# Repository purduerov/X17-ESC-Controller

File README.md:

# X17-ESC-Controller
This board turns signals from the Pi into PWM signals that go to the ESC Adapter

Whenever you make a new part, download the datasheet and save it here _**and**_ with the part in the parts library

Always pull other people's changes before beginning to work
`git pull`

Be sure to push your changes after  working on them. Run:
1. `git add .` to add any files in this directory or a subdirectory
or `git add -u` to add any modified files
2. (Optional) `git clean -nX` to see what ignored files can be removed
	`git clean -fX` removes ignored files (Eagle backups)
3. `git commit -m "helpful commit message"` with a description of the work that you did
4. `git push` to push your work to github

Other helpful commands
* `git status` says information about modified and staged files
* `git log` shows the recent commits of the repository
* `git log filename.extension` show the recent commits for just that file
* `git checkout first-couple-letter-of-commit-id` lets you go back to a previous version
* `git checkout master` brings you back to the latest commit
* `git tag` lists the tags
* `git tag -a orderX -m "the version of the board placed for the X'th order"` tag a specific commit
* `git push --tags` needed to push tags to remote
* `git show orderX` show the commit log for the given tag
* `git checkout orderX` go back and interact with the files at the tagged commit

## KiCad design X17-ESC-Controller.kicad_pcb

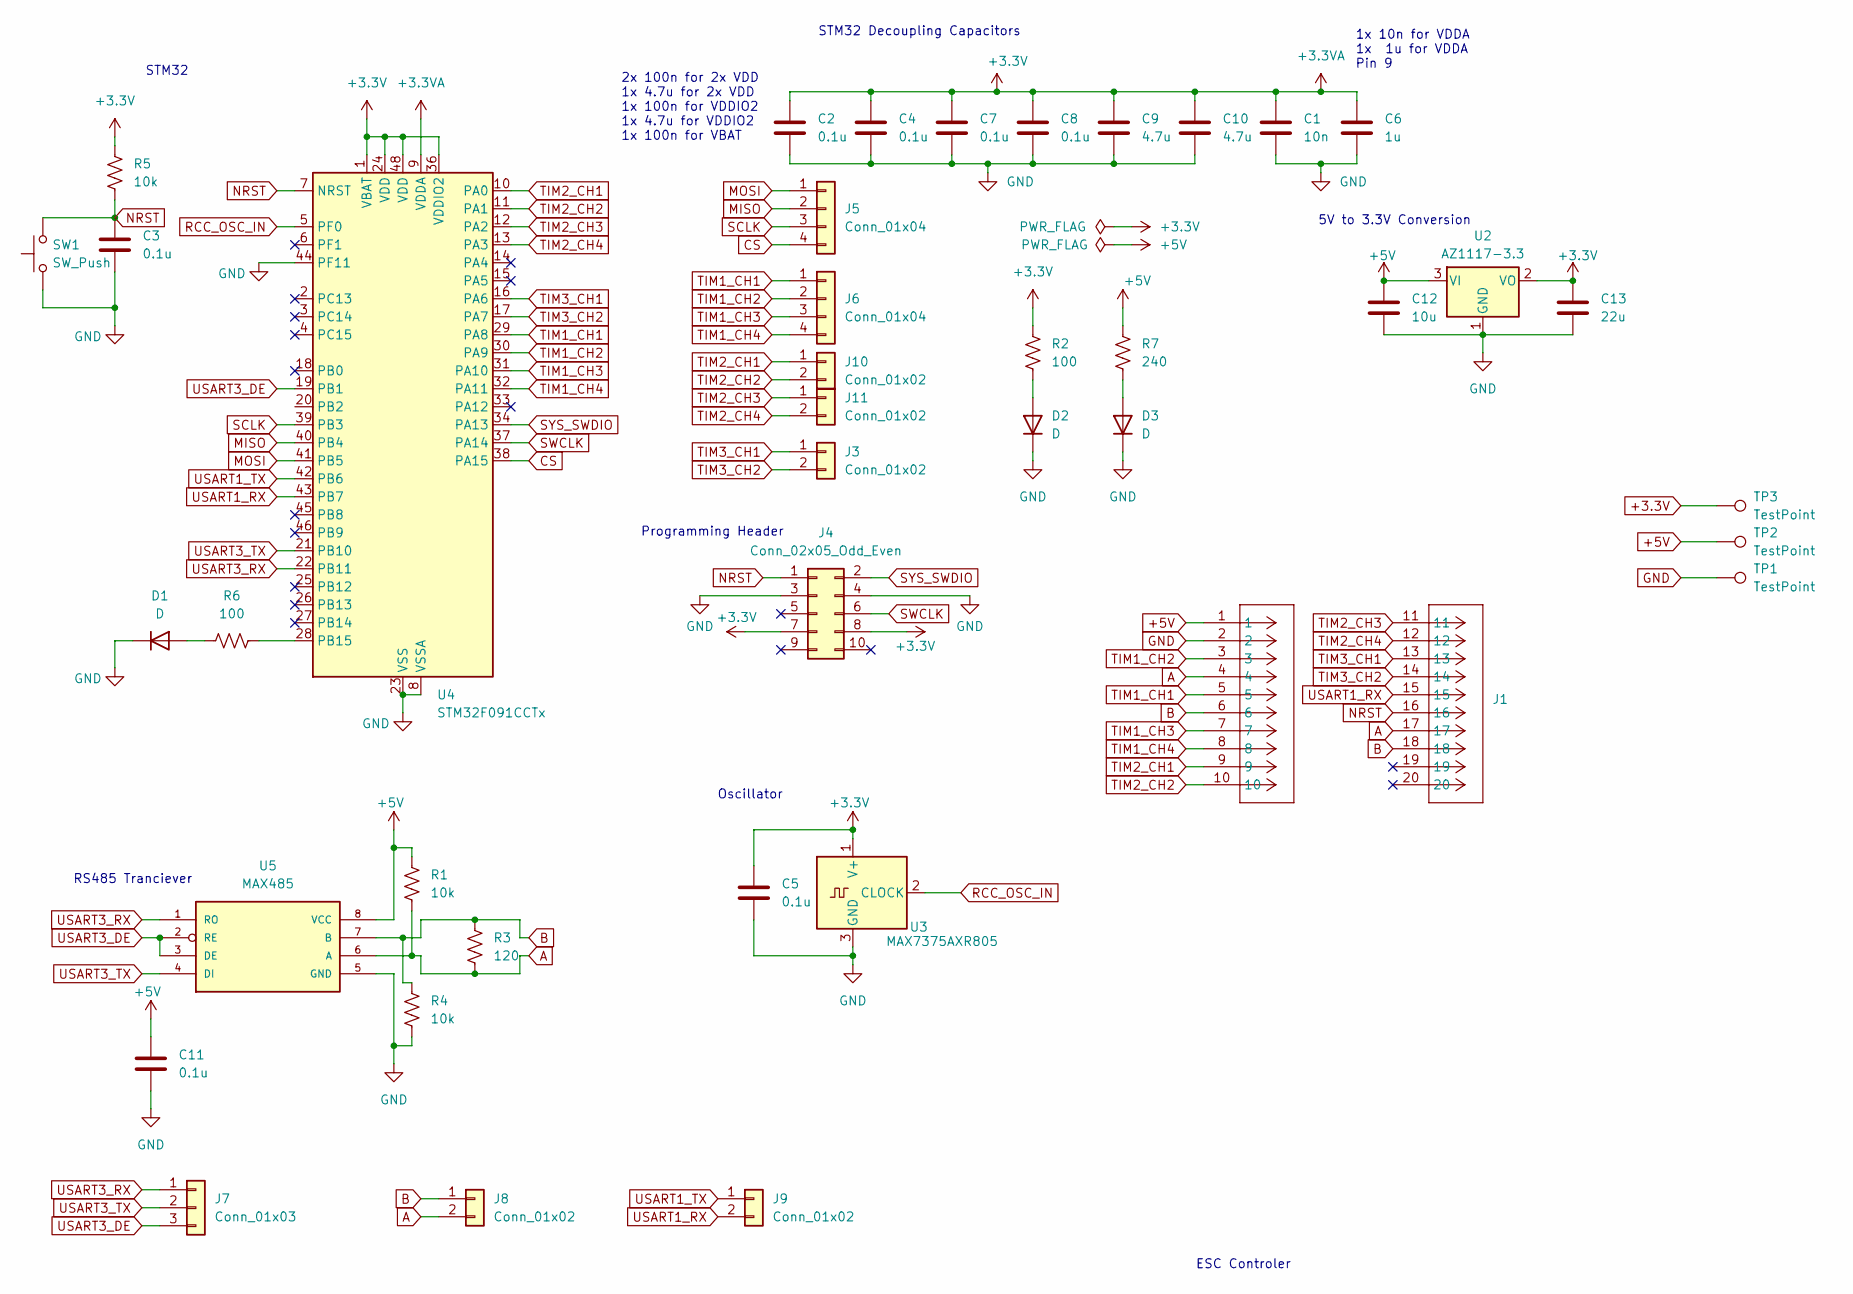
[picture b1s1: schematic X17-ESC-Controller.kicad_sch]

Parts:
C1: 10n; C_0603_1608Metric_Pad1.08x0.95mm_HandSolder
C2, C3, C4, C5, C7, C8, C11: 0.1u; C_0603_1608Metric_Pad1.08x0.95mm_HandSolder
C6: 1u; C_0603_1608Metric_Pad1.08x0.95mm_HandSolder
C9, C10: 4.7u; C_0603_1608Metric_Pad1.08x0.95mm_HandSolder
C12: 10u; C_0603_1608Metric_Pad1.08x0.95mm_HandSolder
C13: 22u; C_0603_1608Metric_Pad1.08x0.95mm_HandSolder
D1, D2, D3: D; LED_0805_2012Metric_Pad1.15x1.40mm_HandSolder
J1: CON10_2X5_UF_DF11_HIR
J3, J8, J9, J10, J11: Conn_01x02; PinHeader_1x02_P2.54mm_Vertical
J4: Conn_02x05_Odd_Even; IDC-Header_2x05_P2.54mm_Vertical
J5, J6: Conn_01x04; PinHeader_1x04_P2.54mm_Vertical
J7: Conn_01x03; PinHeader_1x03_P2.54mm_Vertical
R1, R4, R5: 10k; R_0603_1608Metric_Pad0.98x0.95mm_HandSolder
R2, R6: 100; R_0603_1608Metric_Pad0.98x0.95mm_HandSolder
R3: 120; R_0603_1608Metric_Pad0.98x0.95mm_HandSolder
R7: 240; R_0603_1608Metric_Pad0.98x0.95mm_HandSolder
SW1: SW_Push; SW_FSM2JMTR_TEC
TP1, TP2, TP3: TestPoint; TestPoint_Pad_D4.0mm
U2: AZ1117-3.3; SOT-223-3_TabPin2
U3: MAX7375AXR805; SOT-323_SC-70_Handsoldering
U4: STM32F091CCTx; LQFP-48_7x7mm_P0.5mm
U5: MAX485; SO08

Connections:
+3.3V: C1.1, C2.1, C4.1, C5.1, C6.1, C7.1, C8.1, C9.1, C10.1, C13.1, J4.7, J4.8, R2.2, R5.2, TP3.1, U2.2 (VO), U3.1 (V+), U4.1 (VBAT), U4.9 (VDDA), U4.24 (VDD), U4.36 (VDDIO2), U4.48 (VDD)
+5V: C11.1, C12.1, J1.1, R1.2, R7.2, TP2.1, U2.3 (VI), U5.8 (VCC)
A: J1.4, J1.17, J8.2, R1.1, R3.2, U5.6 (A)
B: J1.6, J1.18, J8.1, R3.1, R4.2, U5.7 (B)
CS: J5.4, U4.38 (PA15)
GND: C1.2, C2.2, C3.2, C4.2, C5.2, C6.2, C7.2, C8.2, C9.2, C10.2, C11.2, C12.2, C13.2, D1.1 (K), D2.1 (K), D3.1 (K), J1.2, J4.3, J4.4, R4.1, SW1.1, TP1.1, U2.1 (GND), U3.3 (GND), U4.8 (VSSA), U4.23 (VSS), U4.35 (VSS), U4.44 (PF11), U4.47 (VSS), U5.5 (GND)
MISO: J5.2, U4.40 (PB4)
MOSI: J5.1, U4.41 (PB5)
NRST: C3.1, J1.16, J4.1, R5.1, SW1.2, U4.7 (NRST)
unnamed: D1.2 (A), R6.1
unnamed: D2.2 (A), R2.1
unnamed: D3.2 (A), R7.1
unnamed: R6.2, U4.28 (PB15)
RCC_OSC_IN: U3.2 (CLOCK), U4.5 (PF0)
SCLK: J5.3, U4.39 (PB3)
SWCLK: J4.6, U4.37 (PA14)
SYS_SWDIO: J4.2, U4.34 (PA13)
TIM1_CH1: J1.5, J6.1, U4.29 (PA8)
TIM1_CH2: J1.3, J6.2, U4.30 (PA9)
TIM1_CH3: J1.7, J6.3, U4.31 (PA10)
TIM1_CH4: J1.8, J6.4, U4.32 (PA11)
TIM2_CH1: J1.9, J10.1, U4.10 (PA0)
TIM2_CH2: J1.10, J10.2, U4.11 (PA1)
TIM2_CH3: J1.11, J11.1, U4.12 (PA2)
TIM2_CH4: J1.12, J11.2, U4.13 (PA3)
TIM3_CH1: J1.13, J3.1, U4.16 (PA6)
TIM3_CH2: J1.14, J3.2, U4.17 (PA7)
USART1_RX: J1.15, J9.2, U4.43 (PB7)
USART1_TX: J9.1, U4.42 (PB6)
USART3_DE: J7.3, U4.19 (PB1), U5.2 (RE), U5.3 (DE)
USART3_RX: J7.1, U4.22 (PB11), U5.1 (RO)
USART3_TX: J7.2, U4.21 (PB10), U5.4 (DI)

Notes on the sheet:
STM32
Programming Header
2x 100n for 2x VDD 1x 4.7u for 2x VDD 1x 100n for VDDIO2 1x 4.7u for VDDIO2 1x 100n for VBAT
1x 10n for VDDA 1x 1u for VDDA Pin 9
5V to 3.3V Conversion
Oscillator
ESC Controler
STM32 Decoupling Capacitors
RS485 Tranciever

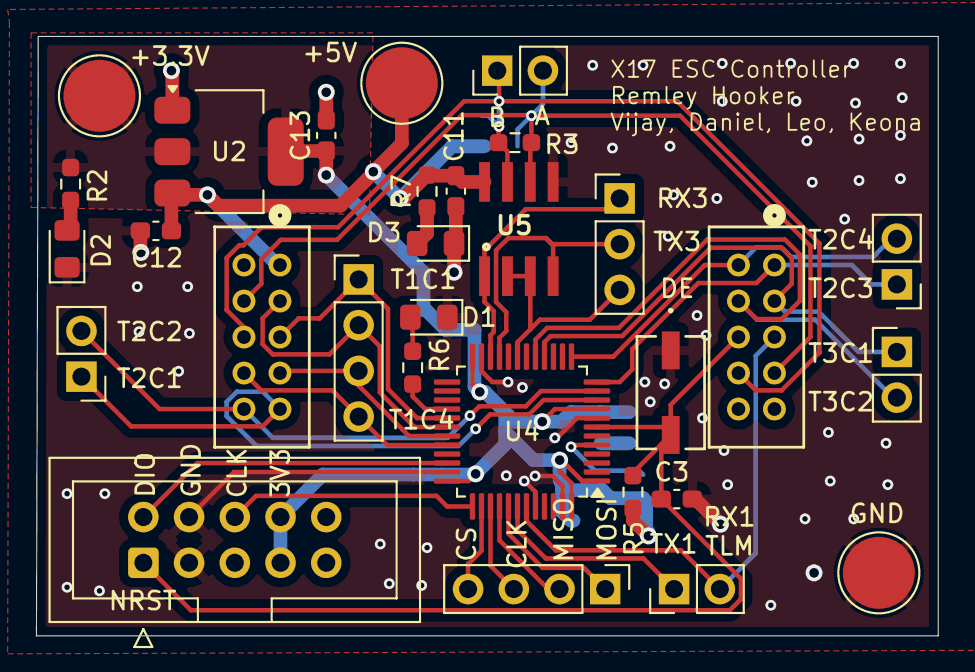
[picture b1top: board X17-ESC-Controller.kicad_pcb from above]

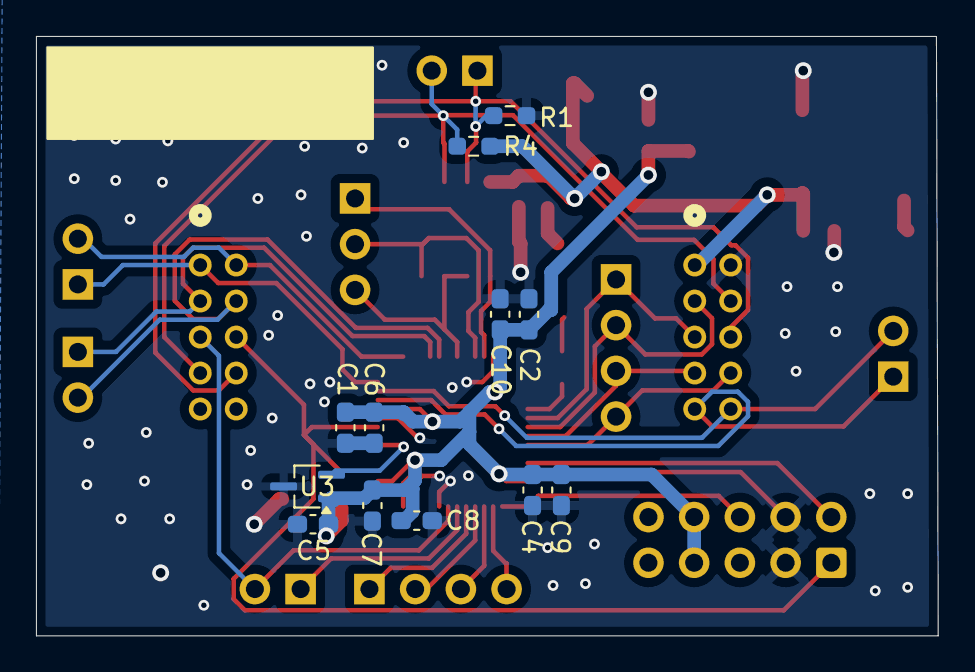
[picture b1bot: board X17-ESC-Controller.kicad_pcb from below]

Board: 2 copper layers, 50.1 x 33.3 mm, 41 parts (12 on the bottom side), 32 nets.

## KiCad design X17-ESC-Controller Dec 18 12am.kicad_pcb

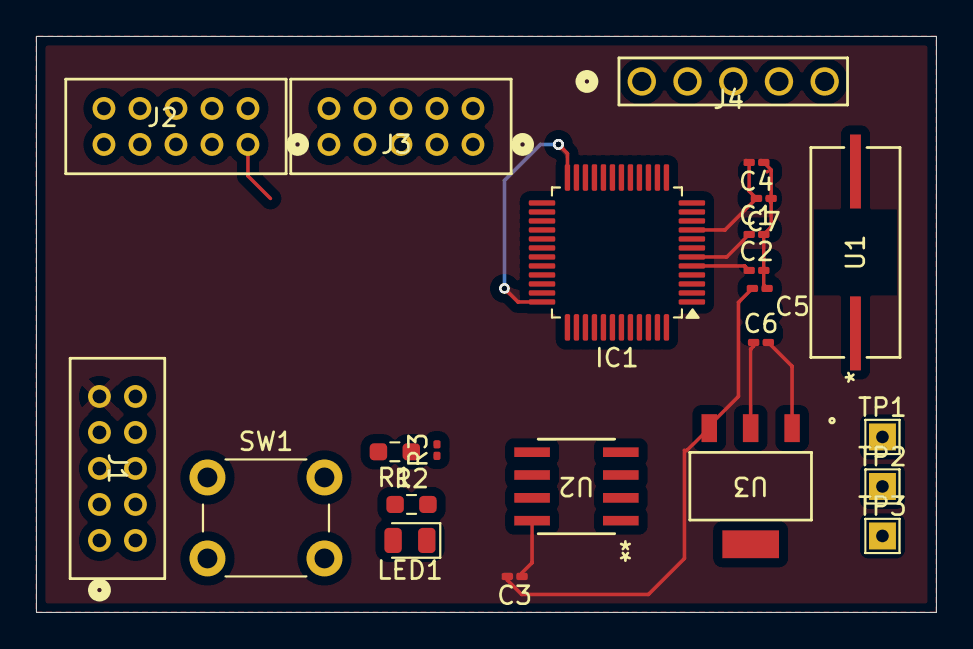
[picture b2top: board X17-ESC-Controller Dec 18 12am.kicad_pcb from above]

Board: 2 copper layers, 50.0 x 32.0 mm, 23 parts (0 on the bottom side), 33 nets.

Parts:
C1, C2: 18pF; C_0201_0603Metric_Pad0.64x0.40mm_HandSolder
C3: CL10B104KB8NNWC; C_0201_0603Metric_Pad0.64x0.40mm_HandSolder
C4, C7: C; C_0201_0603Metric_Pad0.64x0.40mm_HandSolder
C5, C6: GRM188R60G226MEA0D; C_0201_0603Metric_Pad0.64x0.40mm_HandSolder
IC1: STM32F091CCT7; LQFP-48_7x7mm_P0.5mm
J1: CON10_2X5_UF_DF11_HIR
J2, J3: DF11-10DP-2DSA24; CON10_2X5_UF_DF11_HIR
J4: Conn_2Rows-05Pins; CONN_A-4030-05A_MOL
LED1: APT2012SGC; LED_0805_2012Metric
R1: 20k; R_0603_1608Metric_Pad0.98x0.95mm_HandSolder
R2: 4.2k; R_0603_1608Metric_Pad0.98x0.95mm_HandSolder
R3: 10k; R_0201_0603Metric
SW1: SW_Push; SW_PUSH_6mm
TP1, TP2, TP3: TestPoint; TestPoint_THTPad_1.5x1.5mm_Drill0.7mm
U1: 8mHz; ABLS-8.000MHZ-B2-T_ABR
U2: MAX485CSA+T; 21-0041-3-M_90-0096-8L_MXM
U3: SOT223_AZ1117I_6P5X3P5_DIO

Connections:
+5V: C3.2, C5.2, U3.3 (INPUT)
/-3.3V: C6.1, U3.2 (OUTPUT)
/NC: IC1.1 (VBAT), IC1.2 (PC13), IC1.3 (PC14-OSC32_IN), IC1.4 (PC15-OSC32_OUT), IC1.8 (VSSA), IC1.20 (PB2), IC1.25 (PB12), IC1.26 (PB13), IC1.27 (PB14), IC1.35 (VSS_2), IC1.38 (PA15), IC1.39 (PB3), IC1.46 (PB9), IC1.47 (VSS_3), J1.1, J1.5, J1.8, J1.10
A: J2.3, U2.6 (A)
B: J2.4, R1.1, U2.7 (B)
CS: IC1.14 (PA4), J3.10, J4.4
GND: C1.2, C2.2, C4.1, C5.1, C6.2, C7.1, IC1.23 (VSS_1), IC1.44 (PF11-BOOT0), IC1.45 (PB8), IC1.48 (VDD_2), J1.3, J1.4, J4.5, LED1.1, R1.2, SW1.2, TP1.1, U2.5 (GND), U3.1 (ADJ/GND)
LED: IC1.28 (PB15), R2.1
MISO: IC1.16 (PA6), J3.7, J4.2
MOSI: IC1.17 (PA7), J3.8, J4.1
NRST: IC1.7 (NRST), J3.6, R3.2, SW1.1
unnamed: LED1.2, R2.2
unnamed: C3.1, U2.8 (VCC)
RCC_OSC_IN: C2.1, IC1.5 (PF0-OSC_IN), U1.2
RCC_OSC_OUT: C1.1, IC1.6 (PF1-OSC_OUT), U1.1
SCLK: IC1.15 (PA5), J3.9
SWCLK: IC1.37 (PA14), J1.6
SYS_SWDIO: IC1.34 (PA13), J1.2
TIM1_CH1: IC1.29 (PA8), J2.5
TIM1_CH2: IC1.30 (PA9), J2.6
TIM1_CH3: IC1.31 (PA10), J2.7
TIM1_CH4: IC1.32 (PA11), J2.8
TIM2_CH1: IC1.10 (PA0), J2.9
TIM2_CH2: IC1.11 (PA1), J2.10
TIM2_CH3: IC1.12 (PA2), J3.1
TIM2_CH4: IC1.13 (PA3), J3.2
TIM3_CH1: IC1.40 (PB4), J3.3
TIM3_CH2: IC1.41 (PB5), J3.4
USART1_DE: IC1.33 (PA12), U2.2 (*RE), U2.3 (DE)
USART1_RX: IC1.43 (PB7), U2.1 (RO)
USART1_TX: IC1.42 (PB6), U2.4 (DI)
USART3_RX: IC1.22 (PB11), J3.5
VDDA: C4.2, C7.2, IC1.9 (VDDA), IC1.24 (VDD_1), IC1.36 (VDDIO2), J1.7, R3.1

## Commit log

2024-10-17 Add files via upload
    10/16 Schematic
2024-10-26 X17 ESC-Controller
    ESC-Controller Schematic for Alumni Design Review
2024-11-14 X17 Controller Schematic
    Fully updated schematic
2024-11-14 X17 ESC Controller Schematic Updated
    Updated PCB Schematic
2024-11-14 X17 ESC Controller
    Updated Schematic
2024-11-14 added board dimensions
2024-12-17 ESC Controller Layout
    **Before Alumni design review changes, will be updated tonight
2024-12-18 PCB Layout New Component Placement
2024-12-18 Updated Schematic for ESC-Controller 12/18
    - Added decoupling capacitors near power pins of the microcontroller.
    - changed capacitors to 0603 capacitors
    - changed LEDs to 0805
    - changed test pads to through hole
    - made sure to label all frequencies
2024-12-18 X17-ESC-Controller 12/18
2024-12-19 12/17 X-17 ESC-Controller
    -Length matched signal traces (RS485, SPI, etc.)
    -Set power and ground traces to 1mm width
    -Replaced capacitors with 0603 footprint
    -Fixed capacitor footprints to match schematic
    -Added through hole test points for key signals
    -Cleaned up unnecessary wires and connections
2025-01-04 layout fix
2025-01-10 all ordered!
2025-01-12 updated 3d model
2025-02-13 updating
